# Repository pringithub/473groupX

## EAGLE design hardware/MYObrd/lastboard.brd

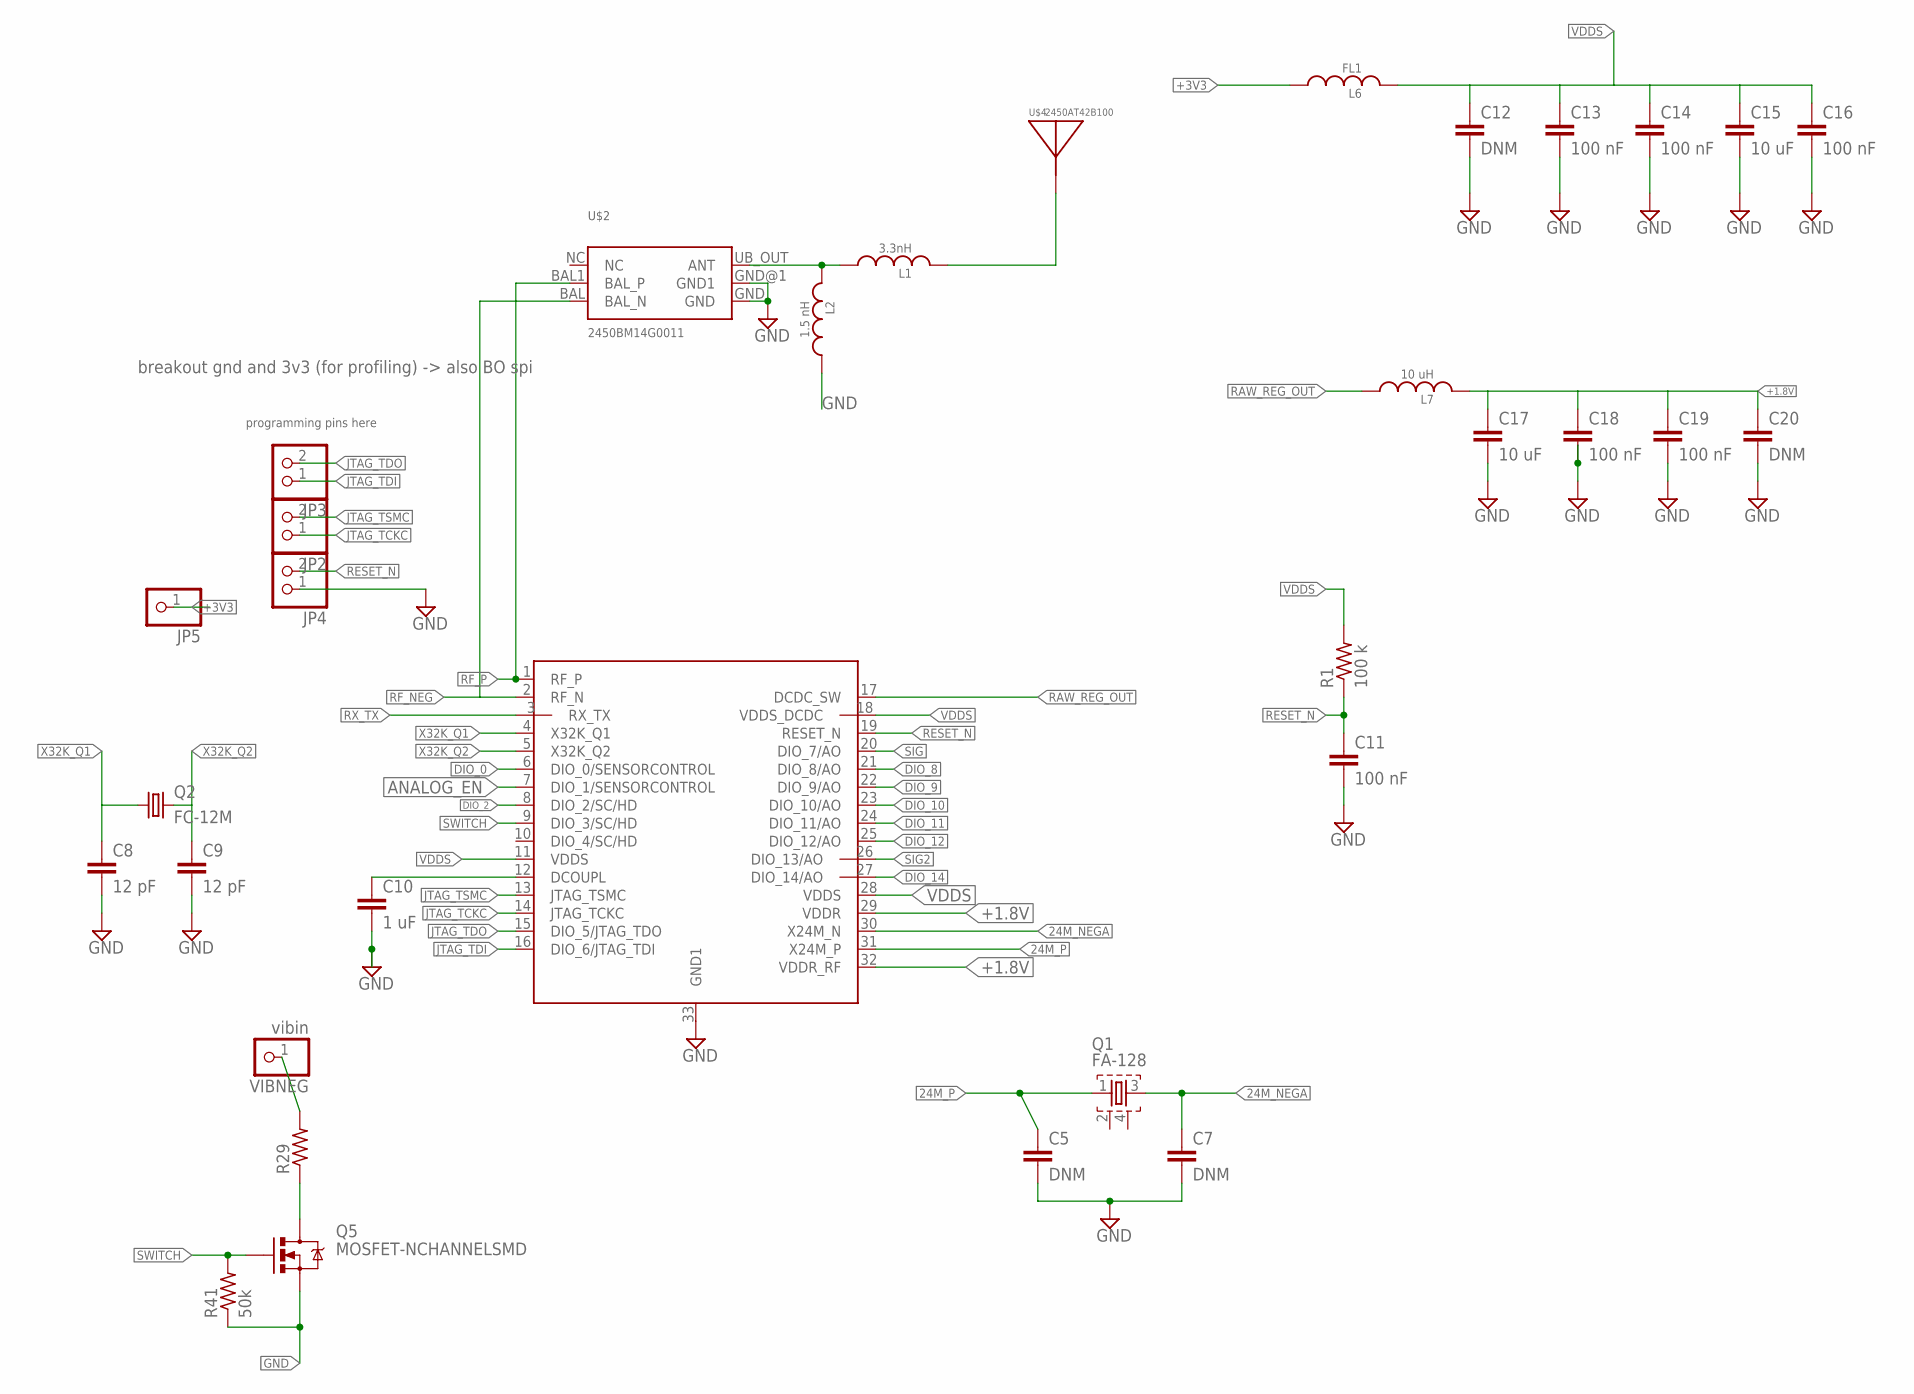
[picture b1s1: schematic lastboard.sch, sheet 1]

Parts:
C5, C7, C12, C20: DNM; C0402
C8, C9: 12 pF; C0402
C10: 1 uF; C0402
C11, C13, C14, C16, C18, C19: 100 nF; C0402
C15, C17: 10 uF; C0402
JP2, JP3, JP4: PINHD-1X2; 1X02
JP5: PINHD-1X1; 1X01
L1: 3.3nH; 0402_CAP
L2: 1.5 nH; 0402_CAP
L6: FL1; 0603_CAP
L7: 10 uH; 0603_CAP
Q1: FA-128
Q2: FC-12M
Q5: MOSFET-NCHANNELSMD; SOT23-3
R1: 100 k; R0402
R29: R-US_R0402; R0402
R41: 50k; R0402
U$1: CC2640-5MM; S-PVQFN-N32
U$2: 2450BM14G0011; DFN/LCC-6
U$4: 2450AT42B100
VIBNEG: vibin; 1X01

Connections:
24M_NEGA: C7.1, Q1.3, U$1.30 (X24M_N)
24M_P: C5.1, Q1.1, U$1.31 (X24M_P)
+1.8V: C17.1, C18.1, C19.1, C20.1, L7.2, U$1.29 (VDDR), U$1.32 (VDDR_RF)
+3V3: JP5.1, L6.1; also elsewhere on the board
ANALOG_EN: U$1.7 (DIO_1/SENSORCONTROL); also elsewhere on the board
DCOUPLE_ME: C10.1, U$1.12 (DCOUPL)
DIO_0: U$1.6 (DIO_0/SENSORCONTROL); also elsewhere on the board
DIO_2: U$1.8 (DIO_2/SC/HD); also elsewhere on the board
DIO_8: U$1.21 (DIO_8/AO)
DIO_9: U$1.22 (DIO_9/AO); also elsewhere on the board
DIO_10: U$1.23 (DIO_10/AO); also elsewhere on the board
DIO_11: U$1.24 (DIO_11/AO); also elsewhere on the board
DIO_12: U$1.25 (DIO_12/AO); also elsewhere on the board
DIO_14: U$1.27 (DIO_14/AO); also elsewhere on the board
GND: C5.2, C7.2, C8.2, C9.2, C10.2, C11.2, C12.2, C13.2, C14.2, C15.2, C16.2, C17.2, C18.2, C19.2, C20.2, JP4.1, L2.1, Q5.2 (S), R41.1, U$1.33 (GND1), U$2.GND, U$2.GND@1 (GND1); also elsewhere on the board
JTAG_TCKC: JP2.1, U$1.14 (JTAG_TCKC)
JTAG_TDI: JP3.1, U$1.16 (DIO_6/JTAG_TDI)
JTAG_TDO: JP3.2, U$1.15 (DIO_5/JTAG_TDO)
JTAG_TSMC: JP2.2, U$1.13 (JTAG_TSMC)
MOTOROUT: R29.2, VIBNEG.1
unnamed: L1.1, L2.2, U$2.UB_OUT (ANT)
unnamed: L1.2, U$4.FEED
unnamed: Q5.3 (D), R29.1
RAW_REG_OUT: L7.1, U$1.17 (DCDC_SW)
RESET_N: C11.1, JP4.2, R1.1, U$1.19 (RESET_N)
RF_NEG: U$1.2 (RF_N), U$2.BAL (BAL_N)
RF_P: U$1.1 (RF_P), U$2.BAL1 (BAL_P)
RX_TX: U$1.3 (RX_TX)
SIG: U$1.20 (DIO_7/AO); also elsewhere on the board
SIG2: U$1.26 (DIO_13/AO); also elsewhere on the board
SWITCH: Q5.1 (G), R41.2, U$1.9 (DIO_3/SC/HD)
VDDS: C12.1, C13.1, C14.1, C15.1, C16.1, L6.2, R1.2, U$1.11 (VDDS), U$1.18 (VDDS_DCDC), U$1.28 (VDDS)
X32K_Q1: C8.1, Q2.1, U$1.4 (X32K_Q1)
X32K_Q2: C9.1, Q2.2, U$1.5 (X32K_Q2)

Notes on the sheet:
programming pins here
breakout gnd and 3v3 (for profiling) -> also BO spi

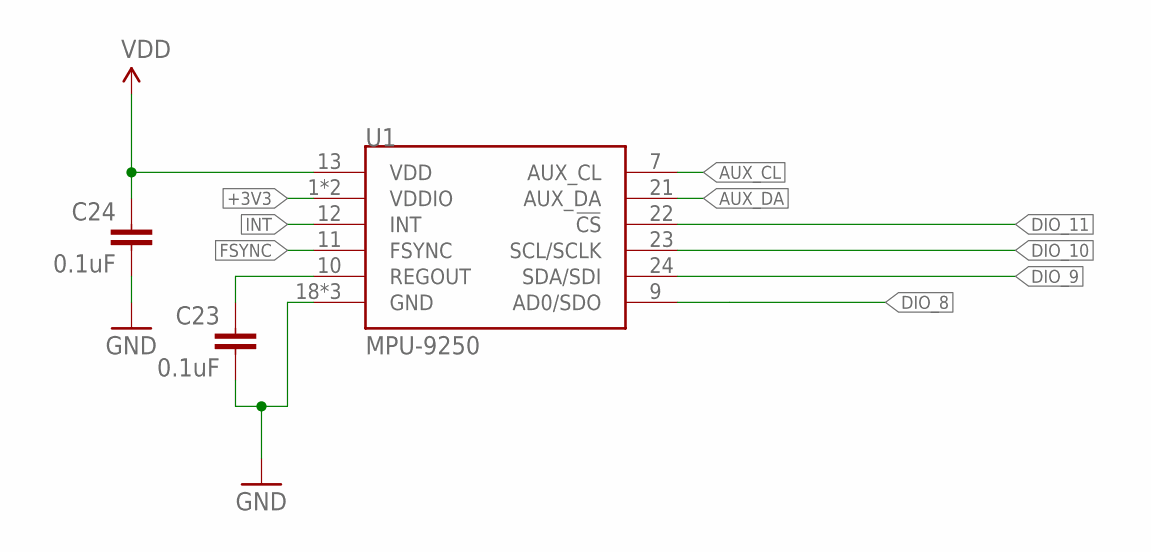
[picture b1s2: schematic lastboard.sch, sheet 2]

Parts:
C23, C24: 0.1uF; 0603-CAP
U1: MPU-9250; QFN24_PAD

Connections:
+3V3: C24.1, U1.1 (VDDIO), U1.8 (VDDIO), U1.13 (VDD); also elsewhere on the board
ADSD_STUB: U1.9 (AD0/SDO)
AUX_CL: U1.7 (AUX_CL)
AUX_DA: U1.21 (AUX_DA)
DIO_9: U1.24 (SDA/SDI); also elsewhere on the board
DIO_10: U1.23 (SCL/SCLK); also elsewhere on the board
DIO_11: U1.22 (!CS); also elsewhere on the board
FSYNC: U1.11 (FSYNC)
GND: C23.2, C24.2, U1.18 (GND), U1.20 (GND), U1.CENTER (GND); also elsewhere on the board
INT: U1.12 (INT)
REGOUT: C23.1, U1.10 (REGOUT)

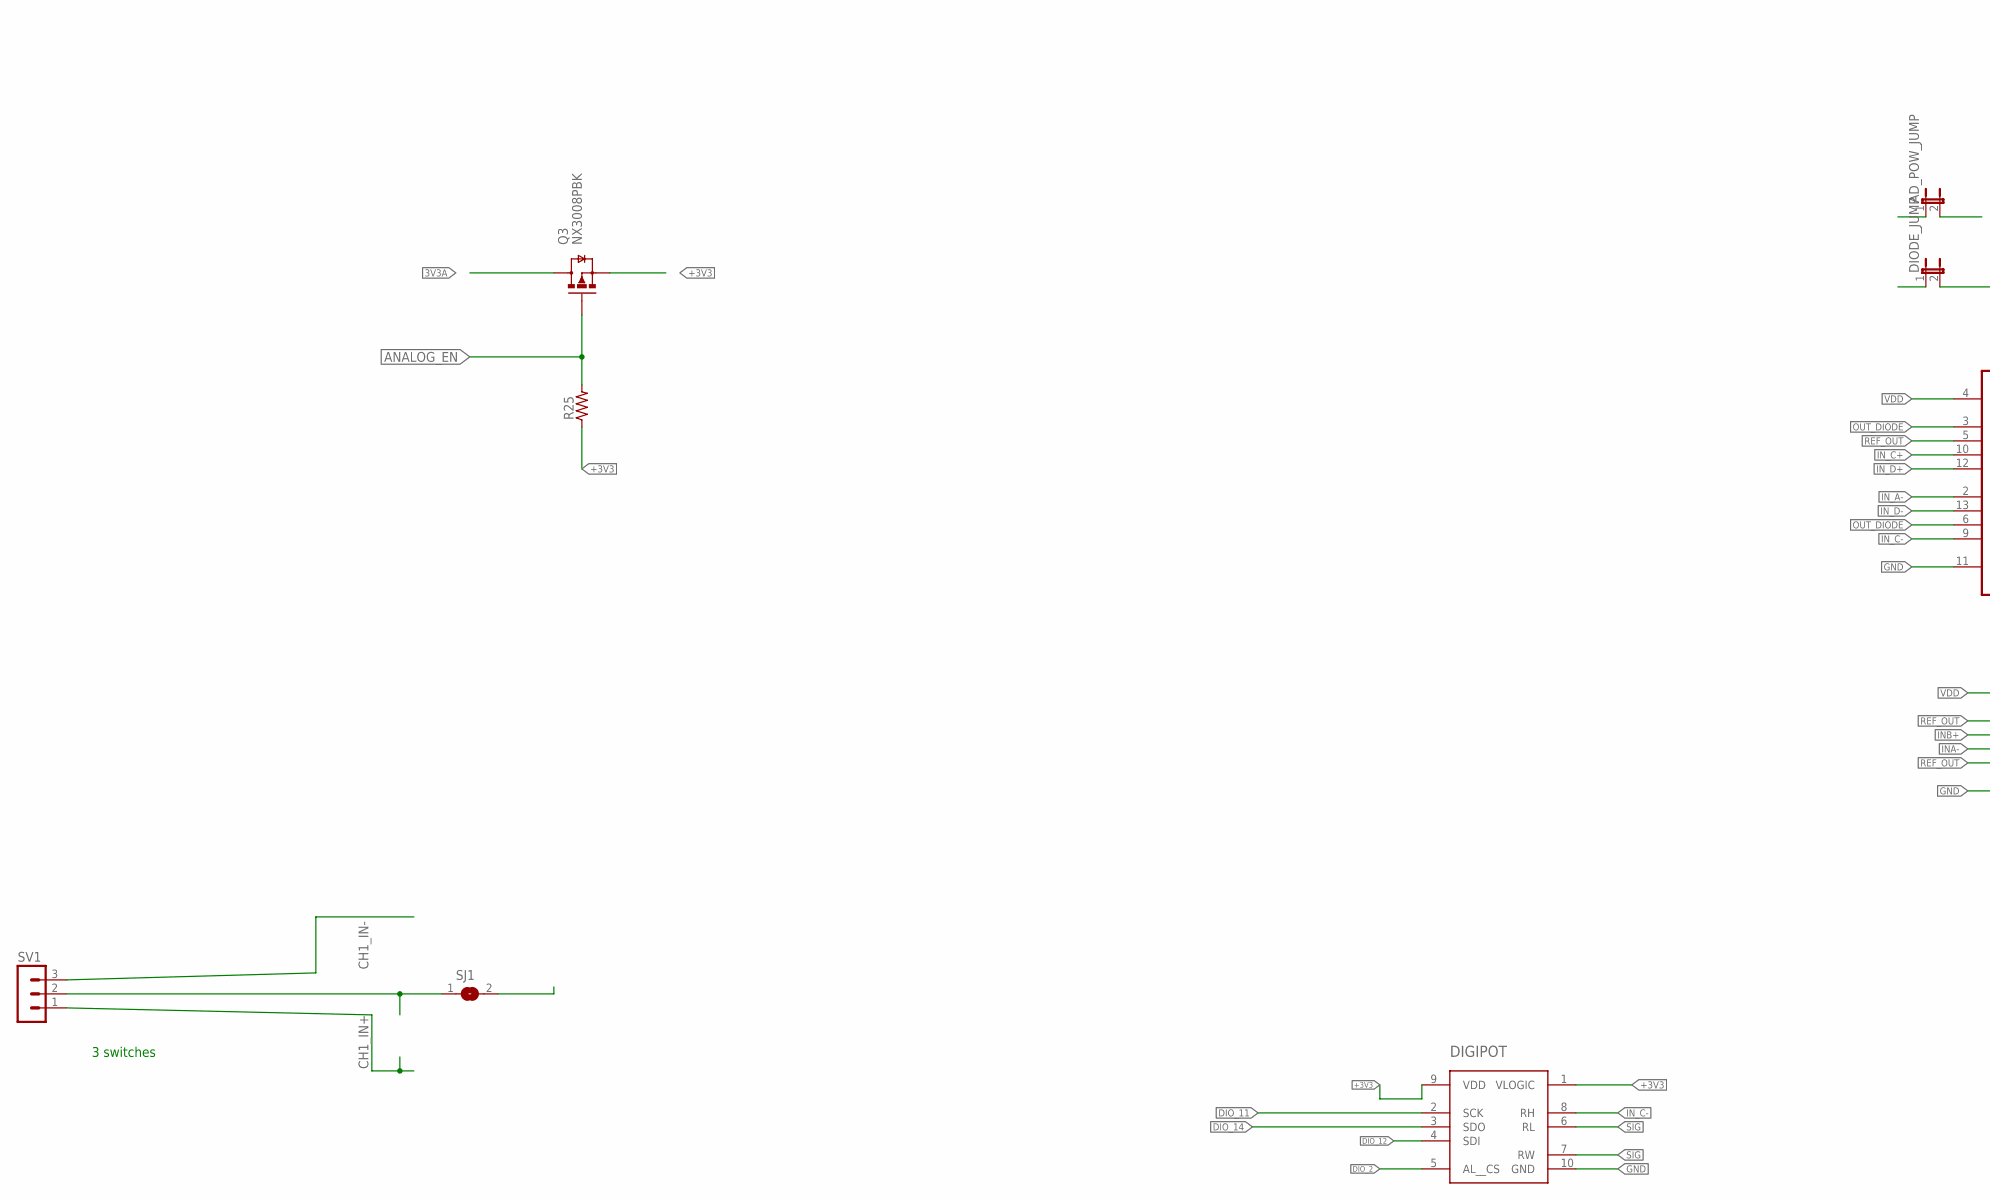
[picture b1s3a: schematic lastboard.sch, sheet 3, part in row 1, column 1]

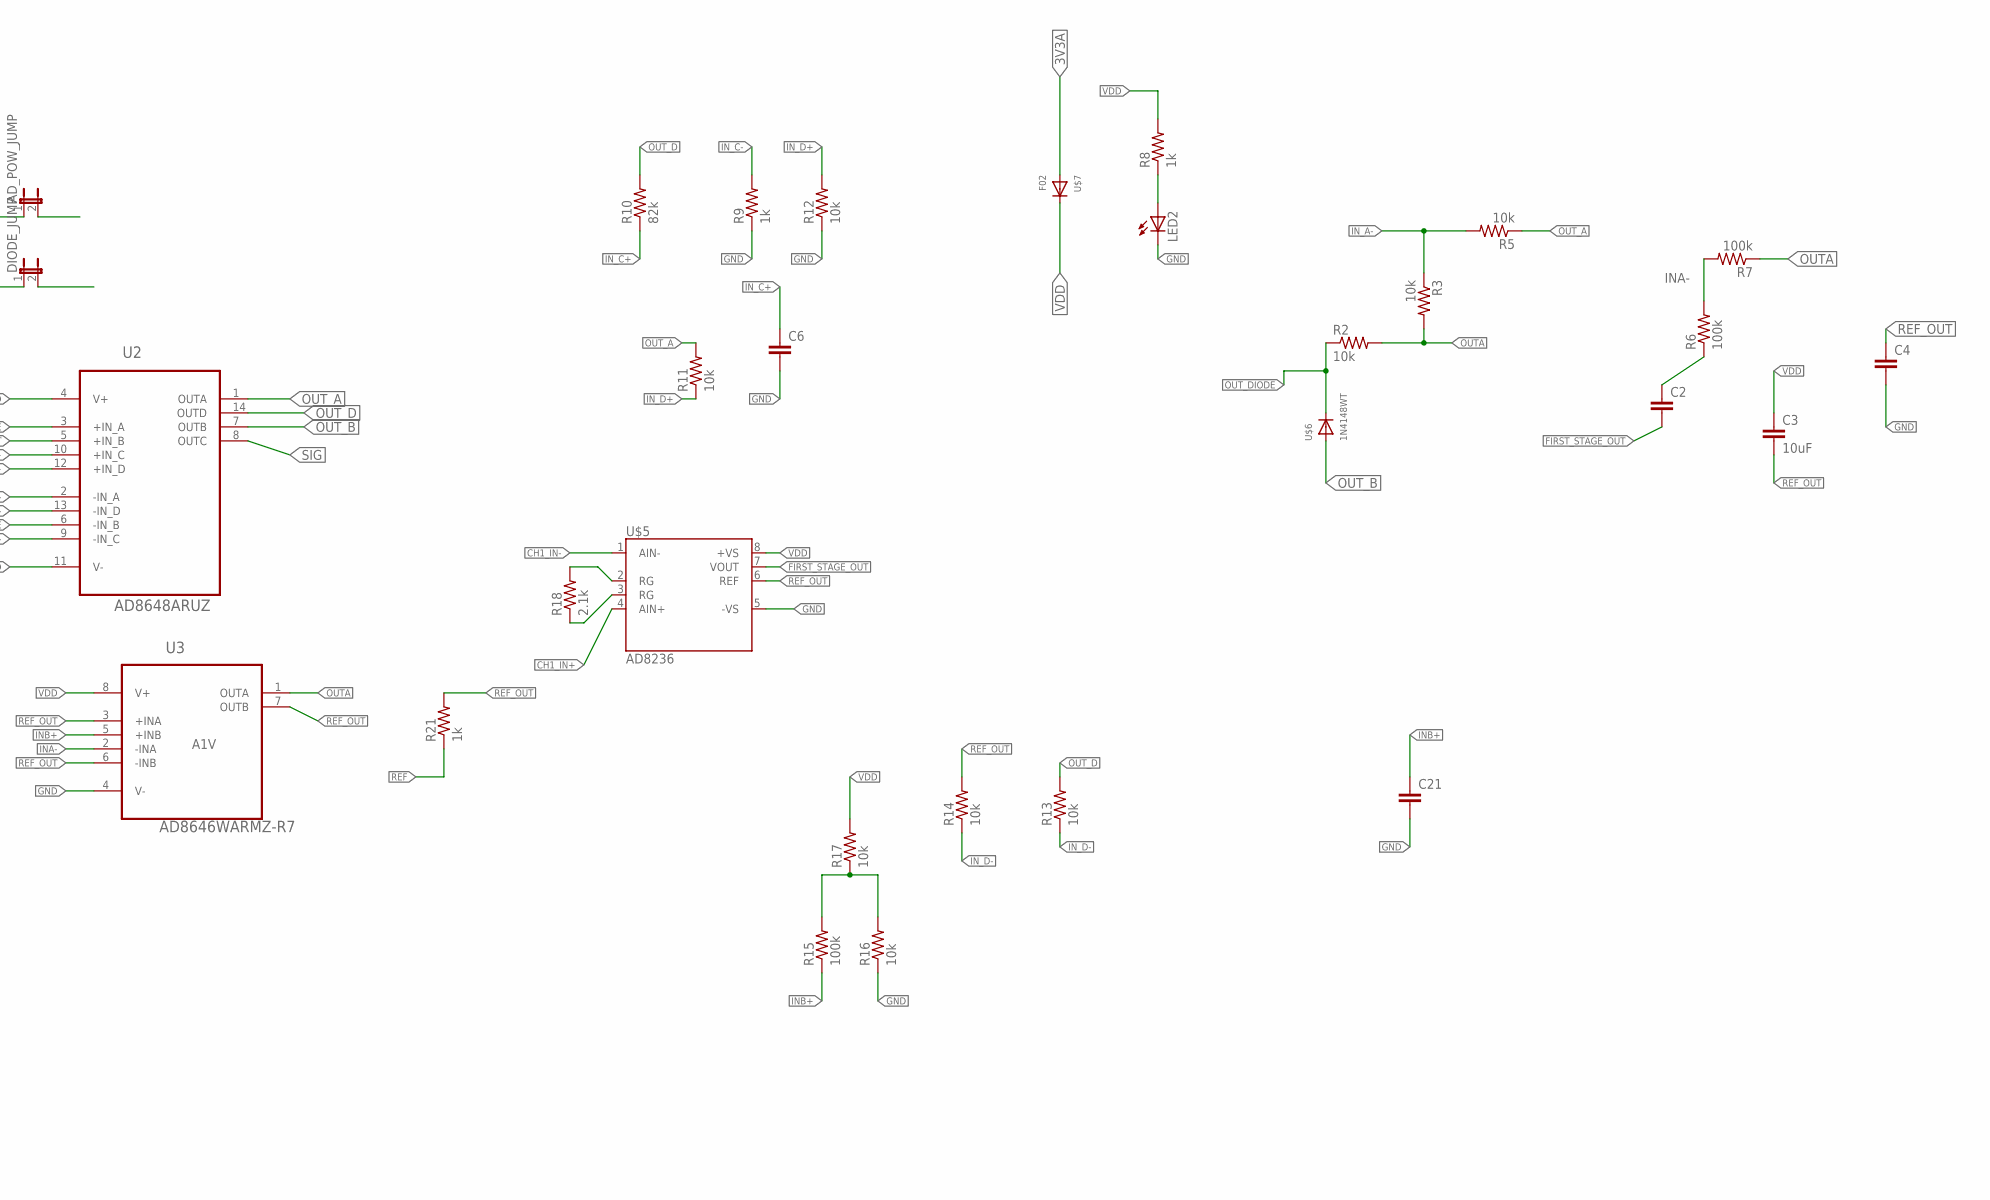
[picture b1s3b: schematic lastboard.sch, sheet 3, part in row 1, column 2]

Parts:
AD_POW_JUMP: JUMPER-2SMD-NO; SJ_2S-NO
C2, C4, C6, C21: C-EUC0603; C0603
C3: 10uF; C0603
DIGIPOT: ISL23418; MSOP10
DIODE_JUMP: JUMPER-2SMD-NO; SJ_2S-NO
LED2: LED0603; LED-0603
Q3: NX3008PBK; SOT23-3
R2, R3, R5, R11, R12, R13, R14, R16, R17: 10k; R0603
R6, R7, R15: 100k; R0603
R8, R9, R21: 1k; R0603
R10: 82k; R0603
R18: 2.1k; R0603
R25: RESISTOR0603_RES; 0603-RES
SJ1: SJ
SV1: MA03-1
U2: AD8648ARUZ; SOP65P640X120-14N
U3: AD8646WARMZ-R7; SOP65P490X110-8N
U$5: AD8236; MSOP8
U$6: 1N4148WT; SOD-523
U$7: F02; SOD-523

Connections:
3V3A: AD_POW_JUMP.2, DIODE_JUMP.1, Q3.3 (D), U$7.A
+3V3: AD_POW_JUMP.1, DIGIPOT.1 (VLOGIC), DIGIPOT.9 (VDD), Q3.2 (S), R25.1; also elsewhere on the board
ANALOG_EN: Q3.1 (G), R25.2; also elsewhere on the board
CH1_IN+: SV1.1, U$5.4 (AIN+)
CH1_IN-: SV1.3, U$5.1 (AIN-)
DIO_2: DIGIPOT.5 (AL__CS); also elsewhere on the board
DIO_11: DIGIPOT.2 (SCK); also elsewhere on the board
DIO_12: DIGIPOT.4 (SDI); also elsewhere on the board
DIO_14: DIGIPOT.3 (SDO); also elsewhere on the board
FIRST_STAGE_OUT: C2.2, U$5.7 (VOUT)
GND: C4.2, C6.2, C21.2, DIGIPOT.10 (GND), LED2.C, R9.1, R12.1, R16.1, U2.11 (V-), U3.4 (V-), U$5.5 (-VS); also elsewhere on the board
INA-: R6.2, R7.2, U3.2 (-INA)
INB+: C21.1, R15.1, U3.5 (+INB)
IN_A-: R3.1, R5.2, U2.2 (-IN_A)
IN_C+: C6.1, R10.1, U2.10 (+IN_C)
IN_C-: DIGIPOT.8 (RH), R9.2, U2.9 (-IN_C)
IN_D+: R11.1, R12.2, U2.12 (+IN_D)
IN_D-: R13.1, R14.1, U2.13 (-IN_D)
unnamed: C2.1, R6.1
unnamed: R18.2, U$5.2 (RG)
unnamed: R15.2, R16.2, R17.1
unnamed: LED2.A, R8.1
unnamed: R18.1, U$5.3 (RG)
OUTA: R2.2, R3.2, R7.1, U3.1 (OUTA)
OUT_A: R5.1, R11.2, U2.1 (OUTA)
OUT_B: U2.7 (OUTB), U$6.A
OUT_D: R10.2, R13.2, U2.14 (OUTD)
OUT_DIODE: R2.1, U2.3 (+IN_A), U2.6 (-IN_B), U$6.K (C)
REF: R21.1, SJ1.1, SV1.2
REF2: SJ1.2; also elsewhere on the board
REF_OUT: C3.2, C4.1, R14.2, R21.2, U2.5 (+IN_B), U3.3 (+INA), U3.6 (-INB), U3.7 (OUTB), U$5.6 (REF)
SIG: DIGIPOT.6 (RL), DIGIPOT.7 (RW), U2.8 (OUTC); also elsewhere on the board
VDD: C3.1, DIODE_JUMP.2, R8.2, R17.2, U2.4 (V+), U3.8 (V+), U$5.8 (+VS), U$7.K (C); also elsewhere on the board

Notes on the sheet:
3 switches
A1V

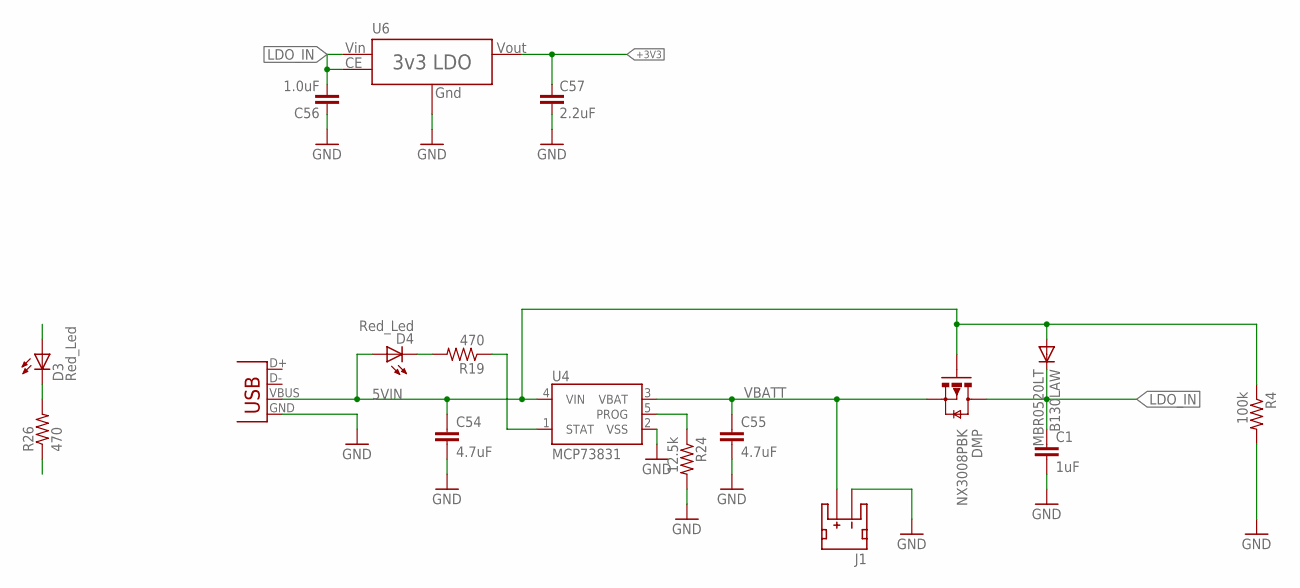
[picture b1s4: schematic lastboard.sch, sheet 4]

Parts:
B130LAW: MBR0520LT; SOD123
C1: 1uF; 0402-CAP
C54, C55: 4.7uF; 0402-CAP
C56: 1.0uF; C0805
C57: 2.2uF; C0805
D3, D4: Red_Led; LED-0603
DMP: NX3008PBK; SOT23-3
J1: JST_2MM_MALE; JST-2-SMD
R4: 100k; 0402-RES
R19, R26: 470; 0402-RES
R24: 12.5k; 0402-RES
U4: MCP73831; SOT23-5
U6: XC6210; SOT-25
X1: USB-MICROB

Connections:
5VIN: B130LAW.A, C54.1, D4.A, DMP.1 (G), R4.1, U4.4 (VIN), X1.VBUS
+3V3: C57.1, U6.5 (VOUT); also elsewhere on the board
ANALOG_EN: D3.A; also elsewhere on the board
GND: C1.2, C54.2, C55.2, C56.1, C57.2, J1.1 (-), R4.2, R24.2, R26.1, U4.2 (VSS), U6.2 (GND), X1.GND; also elsewhere on the board
LDO_IN: B130LAW.C, C1.1, C56.2, DMP.3 (D), U6.1 (VIN), U6.3 (CE)
unnamed: R24.1, U4.5 (PROG)
unnamed: D4.C, R19.2
unnamed: D3.C, R26.2
unnamed: R19.1, U4.1 (STAT)
VBATT: C55.1, DMP.2 (S), J1.2 (+), U4.3 (VBAT)

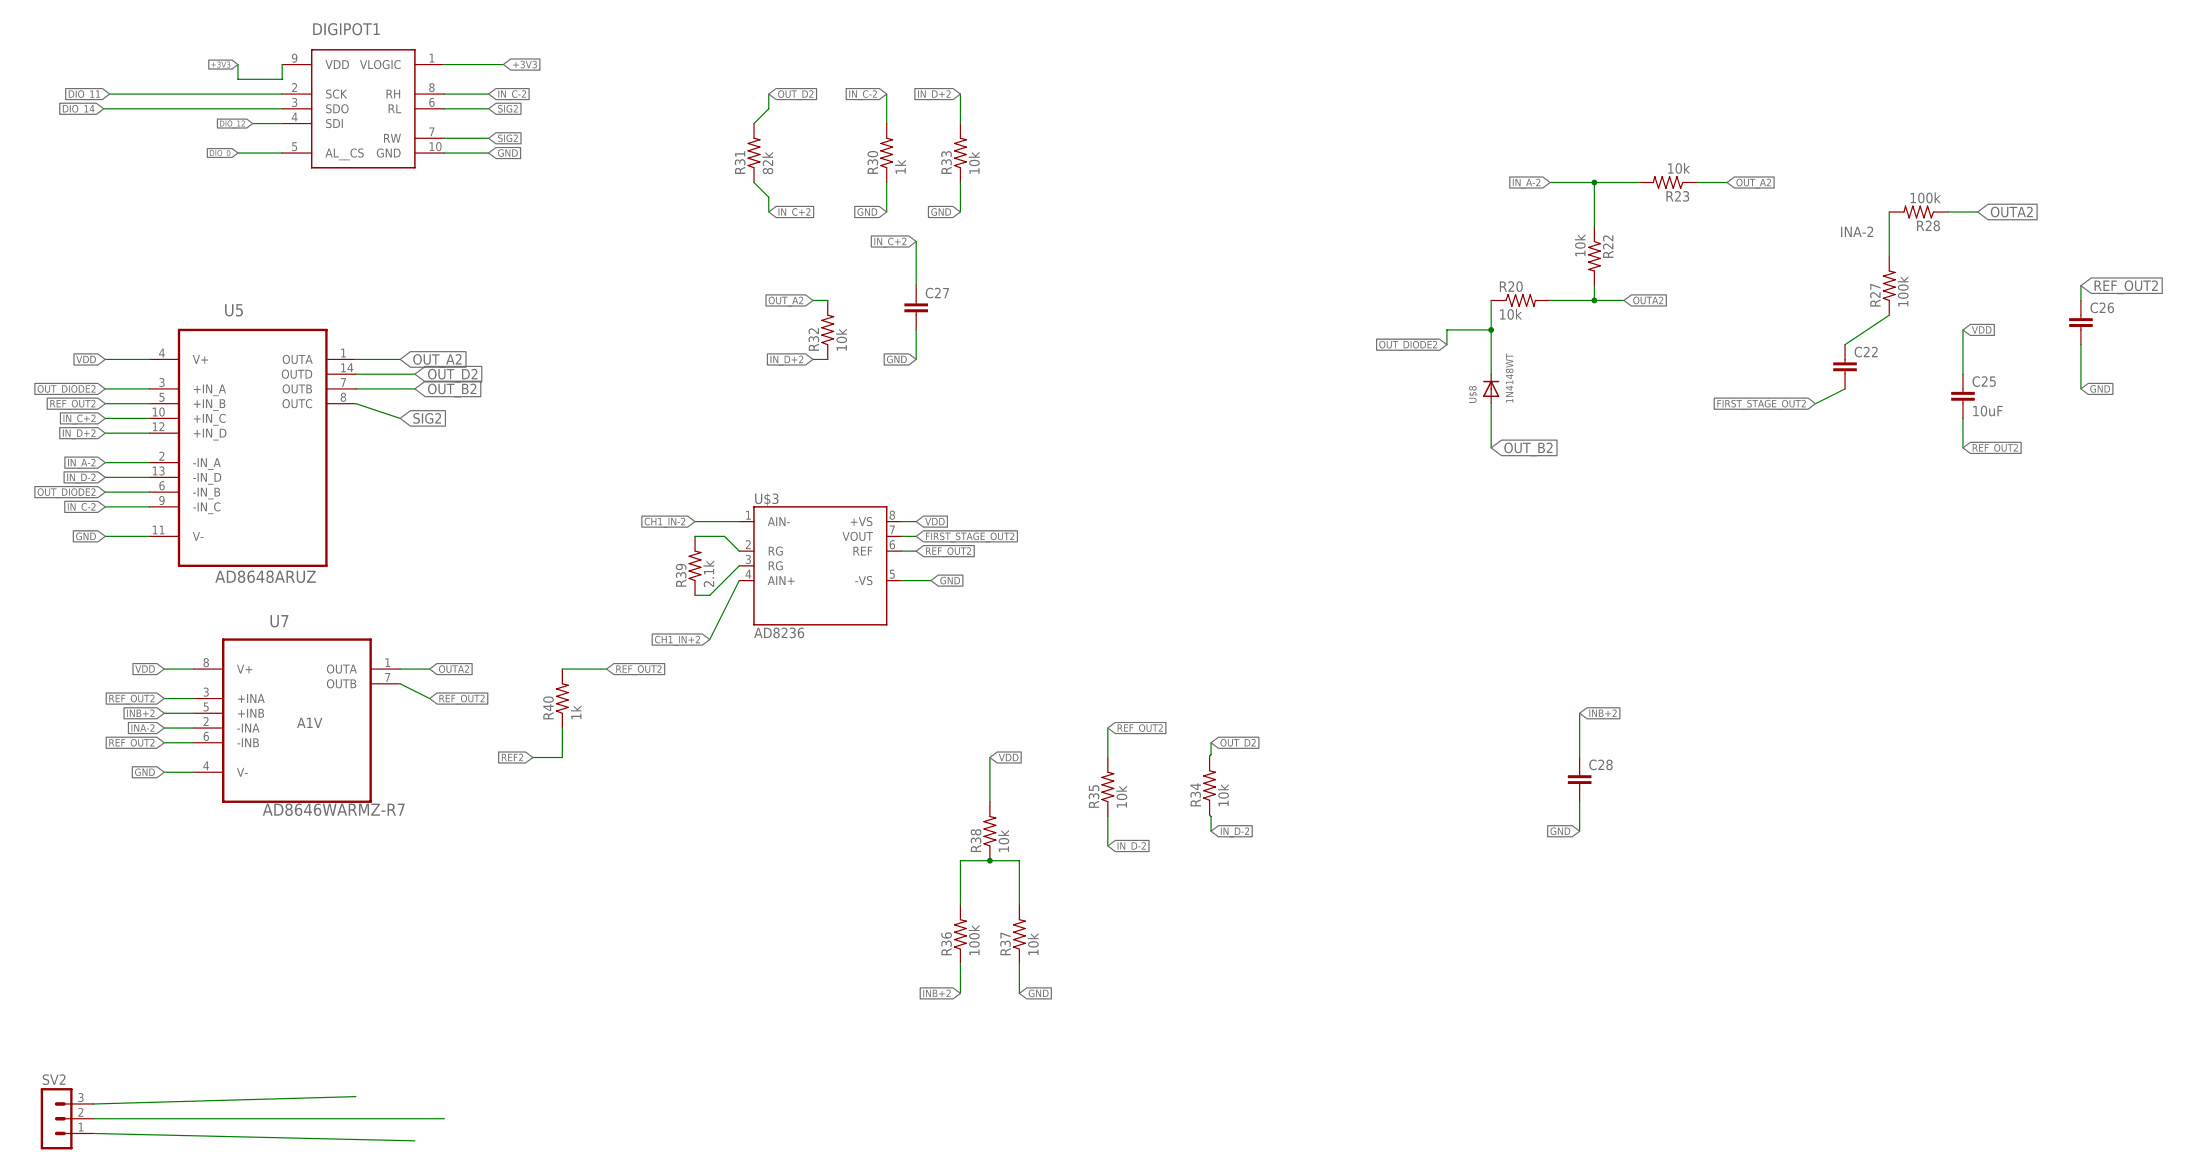
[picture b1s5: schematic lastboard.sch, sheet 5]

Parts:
C22, C26, C27, C28: C-EUC0603; C0603
C25: 10uF; C0603
DIGIPOT1: ISL23418; MSOP10
R20, R22, R23, R32, R33, R34, R35, R37, R38: 10k; R0603
R27, R28, R36: 100k; R0603
R30, R40: 1k; R0603
R31: 82k; R0603
R39: 2.1k; R0603
SV2: MA03-1
U5: AD8648ARUZ; SOP65P640X120-14N
U7: AD8646WARMZ-R7; SOP65P490X110-8N
U$3: AD8236; MSOP8
U$8: 1N4148WT; SOD-523

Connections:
+3V3: DIGIPOT1.1 (VLOGIC), DIGIPOT1.9 (VDD); also elsewhere on the board
CH1_IN+2: SV2.1, U$3.4 (AIN+)
CH1_IN-2: SV2.3, U$3.1 (AIN-)
DIO_0: DIGIPOT1.5 (AL__CS); also elsewhere on the board
DIO_11: DIGIPOT1.2 (SCK); also elsewhere on the board
DIO_12: DIGIPOT1.4 (SDI); also elsewhere on the board
DIO_14: DIGIPOT1.3 (SDO); also elsewhere on the board
FIRST_STAGE_OUT2: C22.2, U$3.7 (VOUT)
GND: C26.2, C27.2, C28.2, DIGIPOT1.10 (GND), R30.1, R33.1, R37.1, U5.11 (V-), U7.4 (V-), U$3.5 (-VS); also elsewhere on the board
INA-2: R27.2, R28.2, U7.2 (-INA)
INB+2: C28.1, R36.1, U7.5 (+INB)
IN_A-2: R22.1, R23.2, U5.2 (-IN_A)
IN_C+2: C27.1, R31.1, U5.10 (+IN_C)
IN_C-2: DIGIPOT1.8 (RH), R30.2, U5.9 (-IN_C)
IN_D+2: R32.1, R33.2, U5.12 (+IN_D)
IN_D-2: R34.1, R35.1, U5.13 (-IN_D)
unnamed: C22.1, R27.1
unnamed: R39.2, U$3.2 (RG)
unnamed: R39.1, U$3.3 (RG)
unnamed: R36.2, R37.2, R38.1
OUTA2: R20.2, R22.2, R28.1, U7.1 (OUTA)
OUT_A2: R23.1, R32.2, U5.1 (OUTA)
OUT_B2: U5.7 (OUTB), U$8.A
OUT_D2: R31.2, R34.2, U5.14 (OUTD)
OUT_DIODE2: R20.1, U5.3 (+IN_A), U5.6 (-IN_B), U$8.K (C)
REF2: R40.1, SV2.2; also elsewhere on the board
REF_OUT2: C25.2, C26.1, R35.2, R40.2, U5.5 (+IN_B), U7.3 (+INA), U7.6 (-INB), U7.7 (OUTB), U$3.6 (REF)
SIG2: DIGIPOT1.6 (RL), DIGIPOT1.7 (RW), U5.8 (OUTC); also elsewhere on the board
VDD: C25.1, R38.2, U5.4 (V+), U7.8 (V+), U$3.8 (+VS); also elsewhere on the board

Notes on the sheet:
A1V

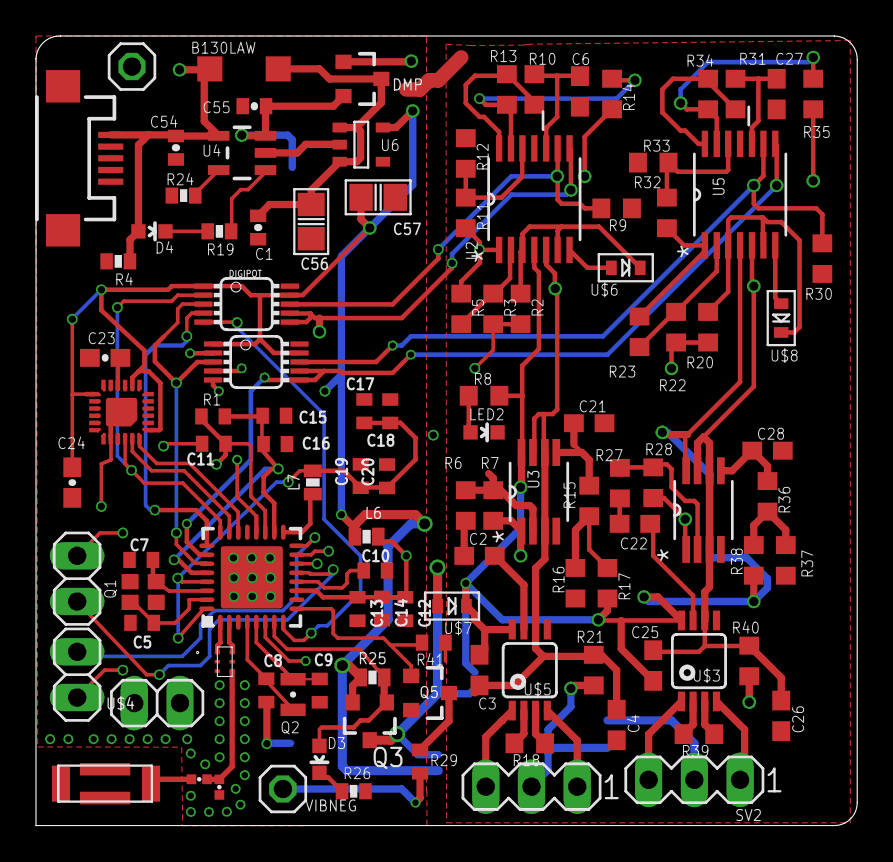
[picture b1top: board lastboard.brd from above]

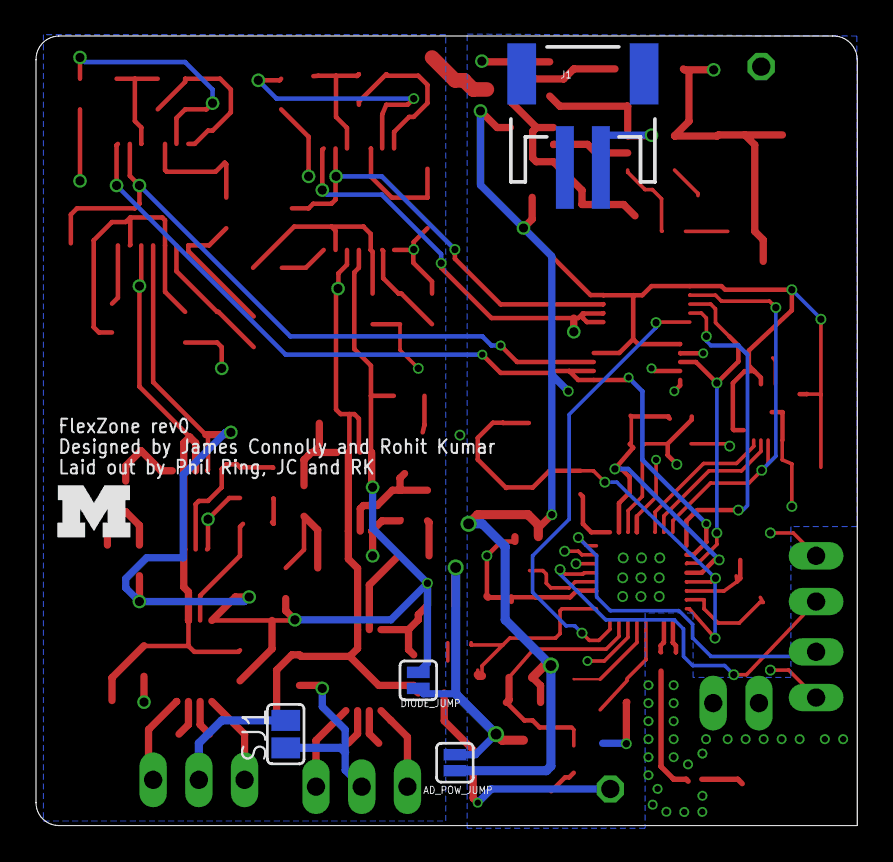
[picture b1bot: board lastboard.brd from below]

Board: 4 copper layers, 45.6 x 43.9 mm, 116 parts (5 on the bottom side), 85 nets.

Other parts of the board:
U$9: BLOCK-M

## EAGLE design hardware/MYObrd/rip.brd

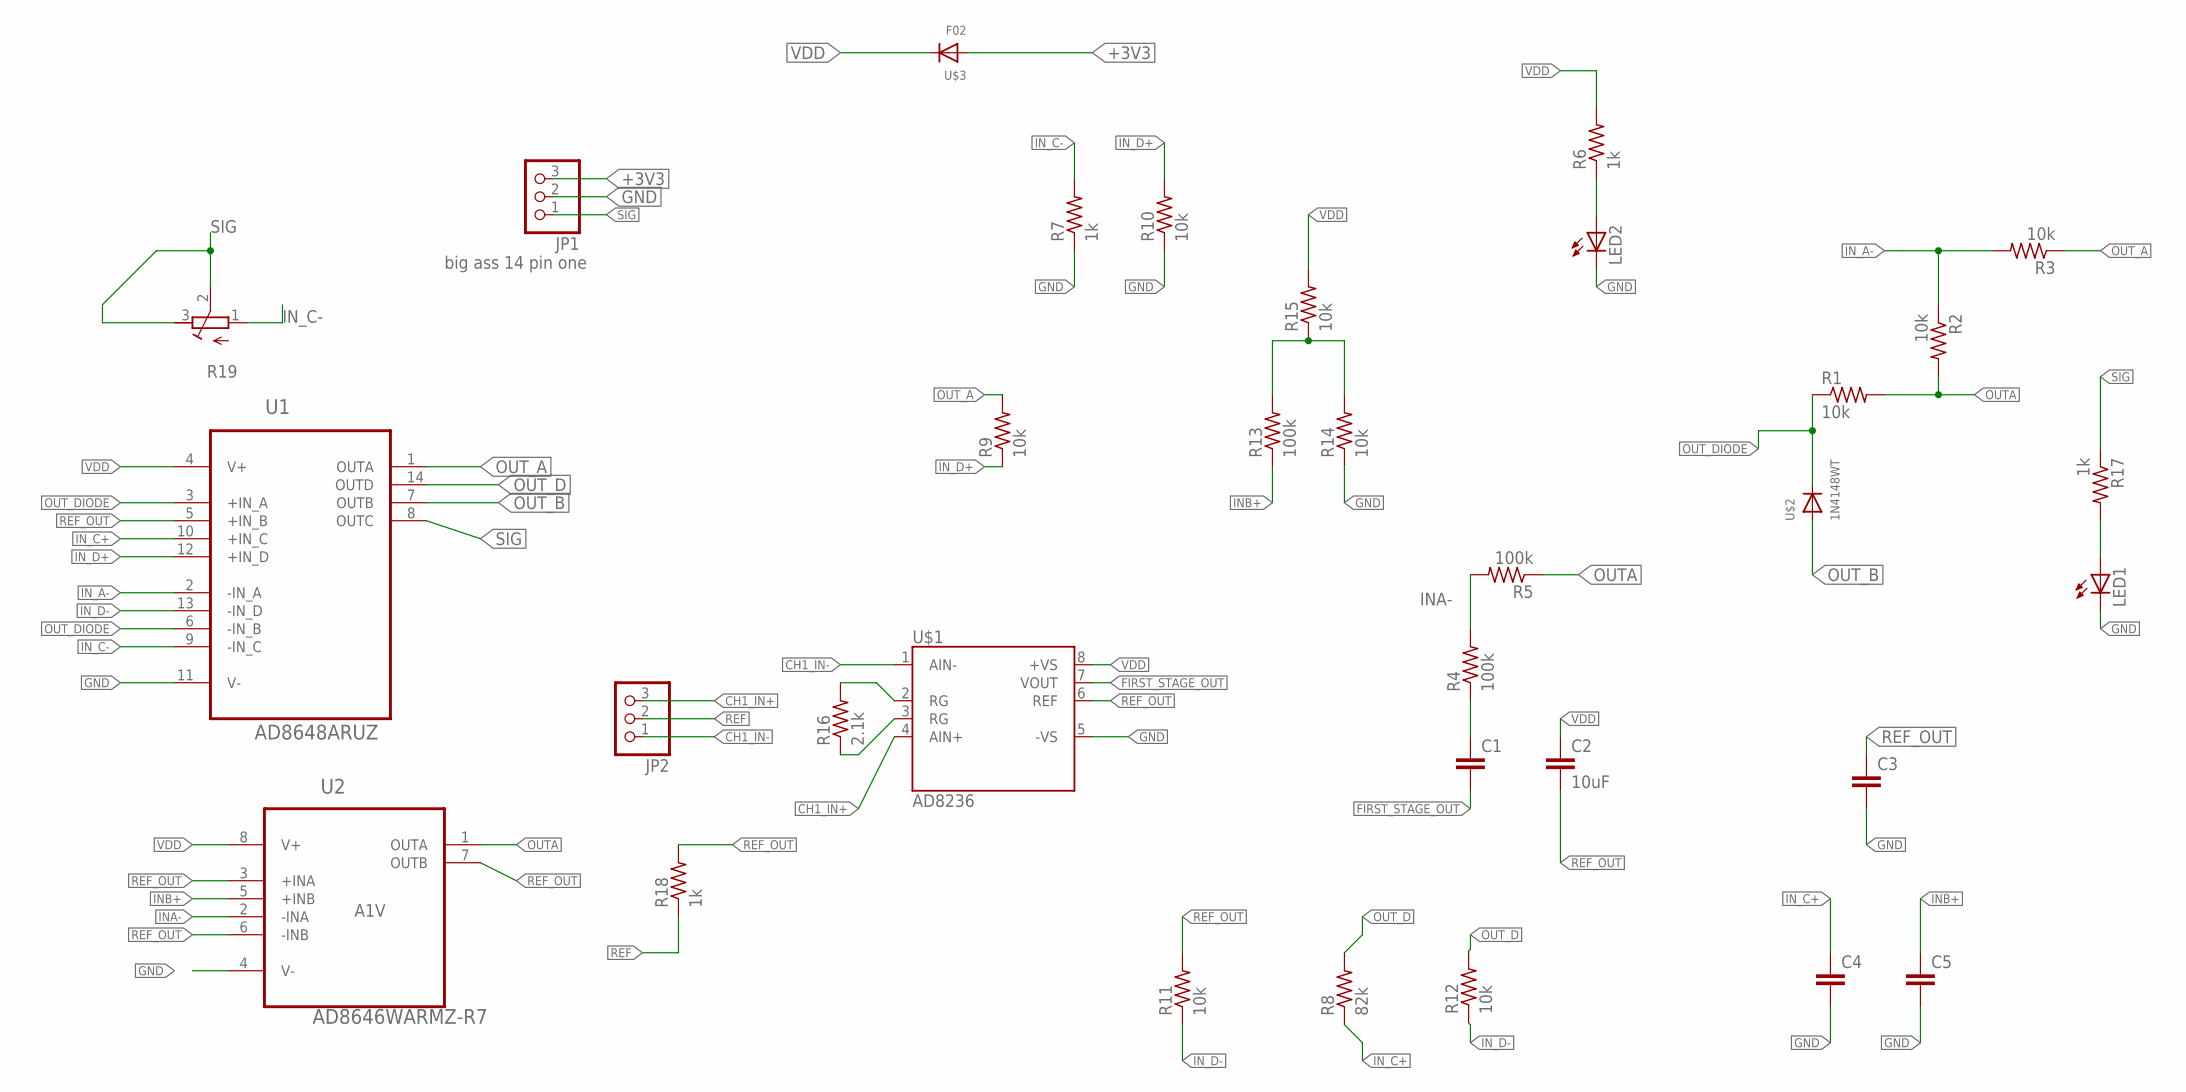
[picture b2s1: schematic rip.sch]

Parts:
C1, C3, C4, C5: C-EUC0603; C0603
C2: 10uF; C0603
JP1, JP2: PINHD-1X3; 1X03
LED1, LED2: LED0603; LED-0603
R1, R2, R3, R9, R10, R11, R12, R14, R15: 10k; R0603
R4, R5, R13: 100k; R0603
R6, R7, R17, R18: 1k; R0603
R8: 82k; R0603
R16: 2.1k; R0603
R19: R-TRIMM3103; RTRIM3103
U1: AD8648ARUZ; SOP65P640X120-14N
U2: AD8646WARMZ-R7; SOP65P490X110-8N
U$1: AD8236; MSOP8
U$2: 1N4148WT; SOD-523
U$3: F02; SOD-523

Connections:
+3V3: JP1.3, U$3.A
CH1_IN+: JP2.3, U$1.4 (AIN+)
CH1_IN-: JP2.1, U$1.1 (AIN-)
FIRST_STAGE_OUT: C1.2, U$1.7 (VOUT)
GND: C3.2, C4.2, C5.2, JP1.2, LED1.C, LED2.C, R7.1, R10.1, R14.1, U1.11 (V-), U2.4 (V-), U$1.5 (-VS)
INA-: R4.2, R5.2, U2.2 (-INA)
INB+: C5.1, R13.1, U2.5 (+INB)
IN_A-: R2.1, R3.2, U1.2 (-IN_A)
IN_C+: C4.1, R8.1, U1.10 (+IN_C)
IN_C-: R7.2, R19.1 (A), U1.9 (-IN_C)
IN_D+: R9.1, R10.2, U1.12 (+IN_D)
IN_D-: R11.1, R12.1, U1.13 (-IN_D)
unnamed: C1.1, R4.1
unnamed: R13.2, R14.2, R15.1
unnamed: LED1.A, R17.2
unnamed: LED2.A, R6.1
unnamed: R16.1, U$1.3 (RG)
unnamed: R16.2, U$1.2 (RG)
OUTA: R1.2, R2.2, R5.1, U2.1 (OUTA)
OUT_A: R3.1, R9.2, U1.1 (OUTA)
OUT_B: U1.7 (OUTB), U$2.A
OUT_D: R8.2, R12.2, U1.14 (OUTD)
OUT_DIODE: R1.1, U1.3 (+IN_A), U1.6 (-IN_B), U$2.K (C)
REF: JP2.2, R18.1
REF_OUT: C2.2, C3.1, R11.2, R18.2, U1.5 (+IN_B), U2.3 (+INA), U2.6 (-INB), U2.7 (OUTB), U$1.6 (REF)
SIG: JP1.1, R17.1, R19.2 (S), R19.3 (E), U1.8 (OUTC)
VDD: C2.1, R6.2, R15.2, U1.4 (V+), U2.8 (V+), U$1.8 (+VS), U$3.K (C)

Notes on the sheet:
big ass 14 pin one
A1V

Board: 2 copper layers, 33 parts (0 on the bottom side), 27 nets, no tracks yet.

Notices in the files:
parts and their libraries:
SparkFun-Capacitors: Licensing: Creative Commons ShareAlike 4.0 International - https://creativecommons.org/licenses/by-sa/4.0
SparkFun-Connectors: Licensing: CC v3.0 Share-Alike You are welcome to use this library for commercial purposes.
